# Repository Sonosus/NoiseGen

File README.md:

# Noise Generator

[![CC BY-SA 4.0][cc-by-sa-shield]][cc-by-sa] 

This is a pink/white noise generator PCB that uses the Electric Druid NOISE2 chip. It is powered with +-12v and is perfect for use in compact synths. It can be used to make a Eurorack/Kosmo module, or in custom synth builds. 

Buy your chips from Electric Druid to help fund their development of future chips like these.

Interactive BOM [here](http://htmlpreview.github.io/?https://github.com/Sonosus/NoiseGen/blob/main/Docs/NoiseGen.html)

This work is licensed under a
[Creative Commons Attribution-ShareAlike 4.0 International License][cc-by-sa].

[![CC BY-SA 4.0][cc-by-sa-image]][cc-by-sa]

[cc-by-sa]: http://creativecommons.org/licenses/by-sa/4.0/
[cc-by-sa-image]: https://licensebuttons.net/l/by-sa/4.0/88x31.png
[cc-by-sa-shield]: https://img.shields.io/badge/License-CC%20BY--SA%204.0-lightgrey.svg

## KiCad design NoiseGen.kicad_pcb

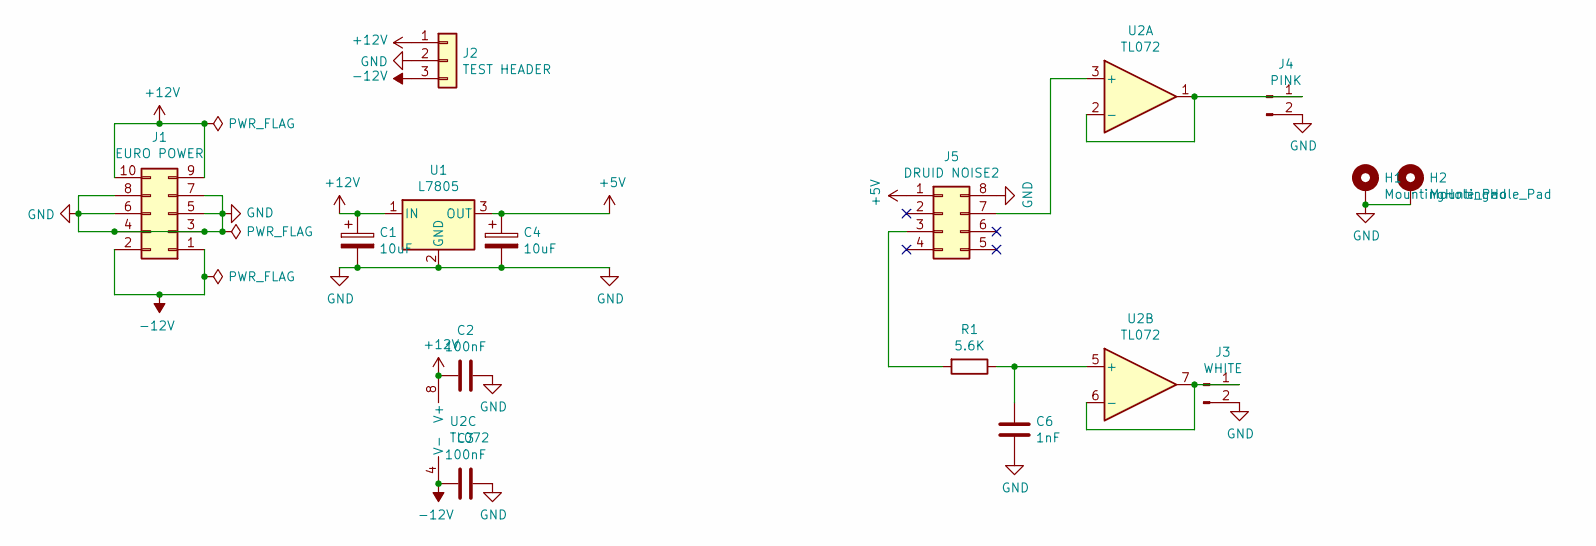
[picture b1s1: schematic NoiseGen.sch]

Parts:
C1, C4: 10uF; CP_Radial_D6.3mm_P2.50mm
C2, C3: 100nF; C_Disc_D6.0mm_W4.4mm_P5.00mm
C6: 1nF; C_Disc_D6.0mm_W4.4mm_P5.00mm
H1, H2: MountingHole_Pad; MountingHole_3.2mm_M3_Pad
J1: EURO POWER; PinHeader_2x05_P2.54mm_Vertical
J2: TEST HEADER; PinHeader_1x03_P2.54mm_Vertical
J3: WHITE; PinHeader_1x02_P2.54mm_Vertical
J4: PINK; PinHeader_1x02_P2.54mm_Vertical
J5: DRUID NOISE2; DIP-8_W7.62mm_Socket_LongPads
R1: 5.6K; R_Axial_DIN0207_L6.3mm_D2.5mm_P7.62mm_Horizontal
U1: L7805; TO-220-3_Vertical
U2: TL072; DIP-8_W7.62mm_Socket_LongPads

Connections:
+5V: C4.1, J5.1, U1.3 (OUT)
+12V: C1.1, C2.1, J1.9, J1.10, J2.1, U1.1 (IN), U2.8 (V+)
-12V: C3.1, J1.1, J1.2, J2.3, U2.4 (V-)
GND: C1.2, C2.2, C3.2, C4.2, C6.2, H1.1, H2.1, J1.3, J1.4, J1.5, J1.6, J1.7, J1.8, J2.2, J3.2, J4.2, J5.8, U1.2 (GND)
unnamed: C6.1, R1.1, U2.5 (+)
unnamed: J3.1, U2.6 (-), U2.7
unnamed: J4.1, U2.1, U2.2 (-)
unnamed: J5.3, R1.2
unnamed: J5.7, U2.3 (+)

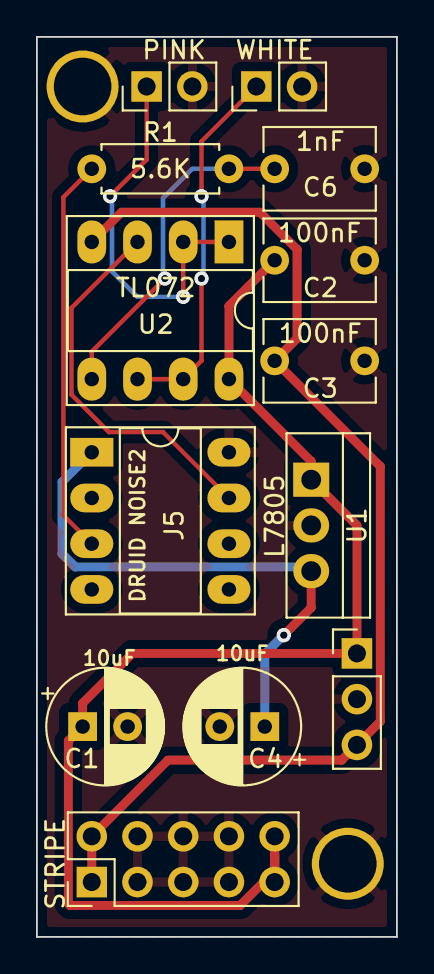
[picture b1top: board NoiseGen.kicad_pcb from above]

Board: 2 copper layers, 20.0 x 50.0 mm, 15 parts (0 on the bottom side), 9 nets.

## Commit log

2021-06-25 add kicad files
2021-06-25 gerbers
2021-06-25 plot schem
2021-06-25 ibom
2021-06-25 add ibom link
2021-09-24 add assembled photo
